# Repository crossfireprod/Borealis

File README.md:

Borealis
==================

WS2812/DMX Light Controller For the [ESPixelStick Firmware](https://github.com/forkineye/ESPixelStick) by Shelby Merrick (forkineye).  Hardware supports both DMX (RS-485) and Pixel (WS2811/WS2812) output modes.

**Key Features**
* The [NodeMCU](https://en.wikipedia.org/wiki/NodeMCU) DEVKIT 1.0 was chosen due to pricepoint, availability, form factor, and onboard 3.3v power supply / USB interface (programmer).  
* Either a DC barrel jack or 5.08mm pluggable terminals may be used to supply power.  
* Output power and data is provided via 5.08mm pluggable terminal blocks.  
* PTC is used in lieu of a traditional fuse.  
* Drill hole in PCB allows for use of reverse firing activity LED, if desired.

Bill Of Materials
-------------------

A Bill Of Materials detailing the specific parts used in our most recent production run can be found on Octopart.  Pricing is more or less optimized around single unit quanties.

* [Pixel (WS2811/WS2812) Version](https://octopart.com/bom-tool/HFxE4Ql2)
* [DMX (RS-485) Version](https://octopart.com/bom-tool/G0dtO20q)

Note: If desired, boards can be populated for both DMX and Pixel use.  (Output mode defined by firmware configuration.)

Repository Contents
-------------------

* **/Hardware** - Eagle Schematic & PCB Layout
* **/Software** - [Platformio](http://platformio.org/) project containing [ESPixelStick Firmware](https://github.com/forkineye/ESPixelStick).
* **/Images** - Images of the schematic / PCB design, as well as a fully assembled unit.

License
-------------------

All contents of this repository are released under [Creative Commons Share-alike 4.0](http://creativecommons.org/licenses/by-sa/4.0/).

Design By: Greg Pohodich & [*ZachCross.com*](https://ZachCross.com)

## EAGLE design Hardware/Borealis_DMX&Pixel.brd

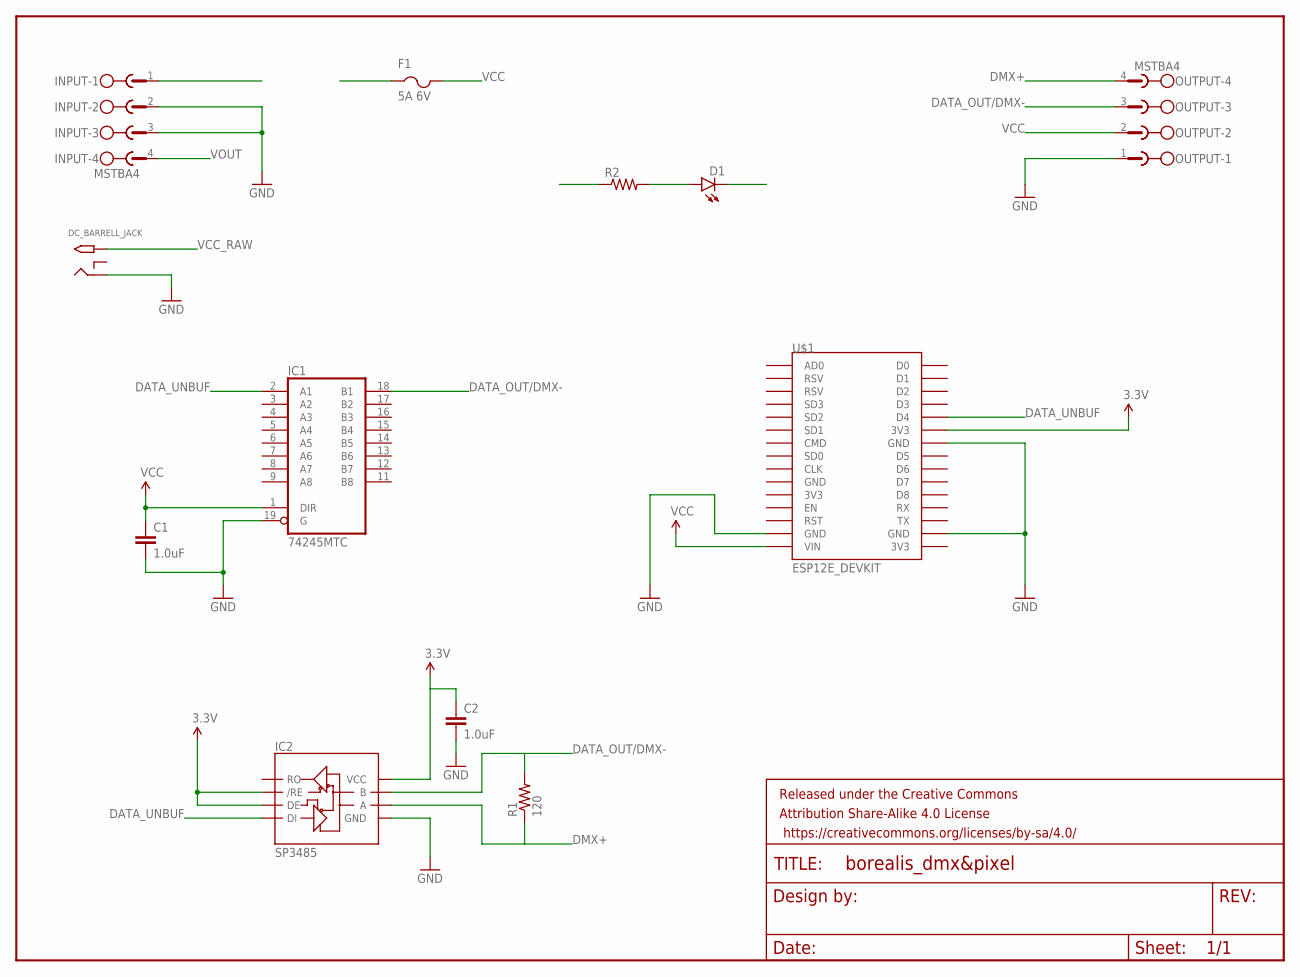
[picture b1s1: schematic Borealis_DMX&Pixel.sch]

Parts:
C1, C2: 1.0uF; 0603-CAP
D1: LED1206-BOTTOM; LED-1206-BOTTOM
DC_BARRELL_JACK: 2.1MMJACKTHM; PJ-102A
F1: 5A 6V; R1206
FRAME1: FRAME-LETTERNO_PACKAGE; DUMMY
IC1: 74245MTC; SSOP20
IC2: SP3485; SO08
INPUT: MSTBA4
OUTPUT: MSTBA4
R1: 120; 0603-RES
R2: RESISTOR0603-RES; 0603-RES
U$1: ESP12E_DEVKIT; DEV_LAYOUT

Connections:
3.3V: C2.1, IC2.2 (/RE), IC2.3 (DE), IC2.8 (VCC), U$1.3V3@1 (3V3)
DATA_OUT/DMX-: IC1.18 (B1), IC2.7 (B), OUTPUT.3, R1.2
DATA_UNBUF: IC1.2 (A1), IC2.4 (DI), U$1.D4
DMX+: IC2.6 (A), OUTPUT.4, R1.1
GND: C1.2, C2.2, D1.C, DC_BARRELL_JACK.RING, IC1.10 (GND), IC1.19 (G), IC2.5 (GND), INPUT.2, INPUT.3, OUTPUT.1, U$1.GND@1 (GND), U$1.GND@2 (GND), U$1.GND@3 (GND)
LED_PWR: D1.A, R2.2
VCC: C1.1, F1.2, IC1.1 (DIR), IC1.20 (VCC), OUTPUT.2, R2.1, U$1.VIN
VCC_RAW: DC_BARRELL_JACK.TIP, F1.1, INPUT.1
VOUT: INPUT.4

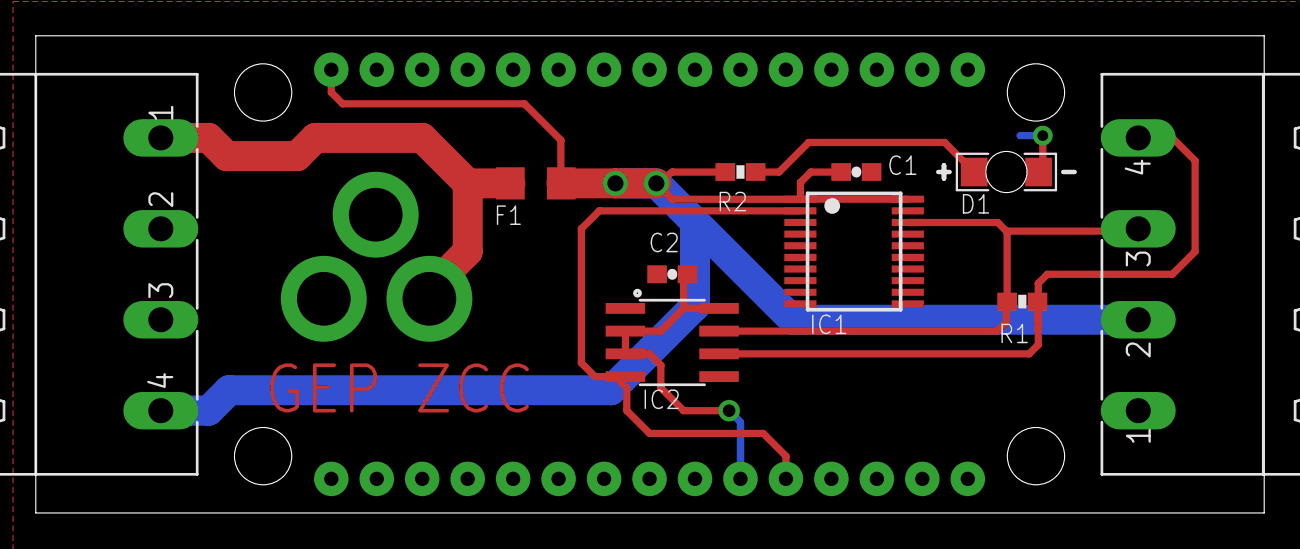
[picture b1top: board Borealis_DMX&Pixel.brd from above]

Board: 2 copper layers, 68.6 x 26.7 mm, 13 parts (1 on the bottom side), 8 nets.

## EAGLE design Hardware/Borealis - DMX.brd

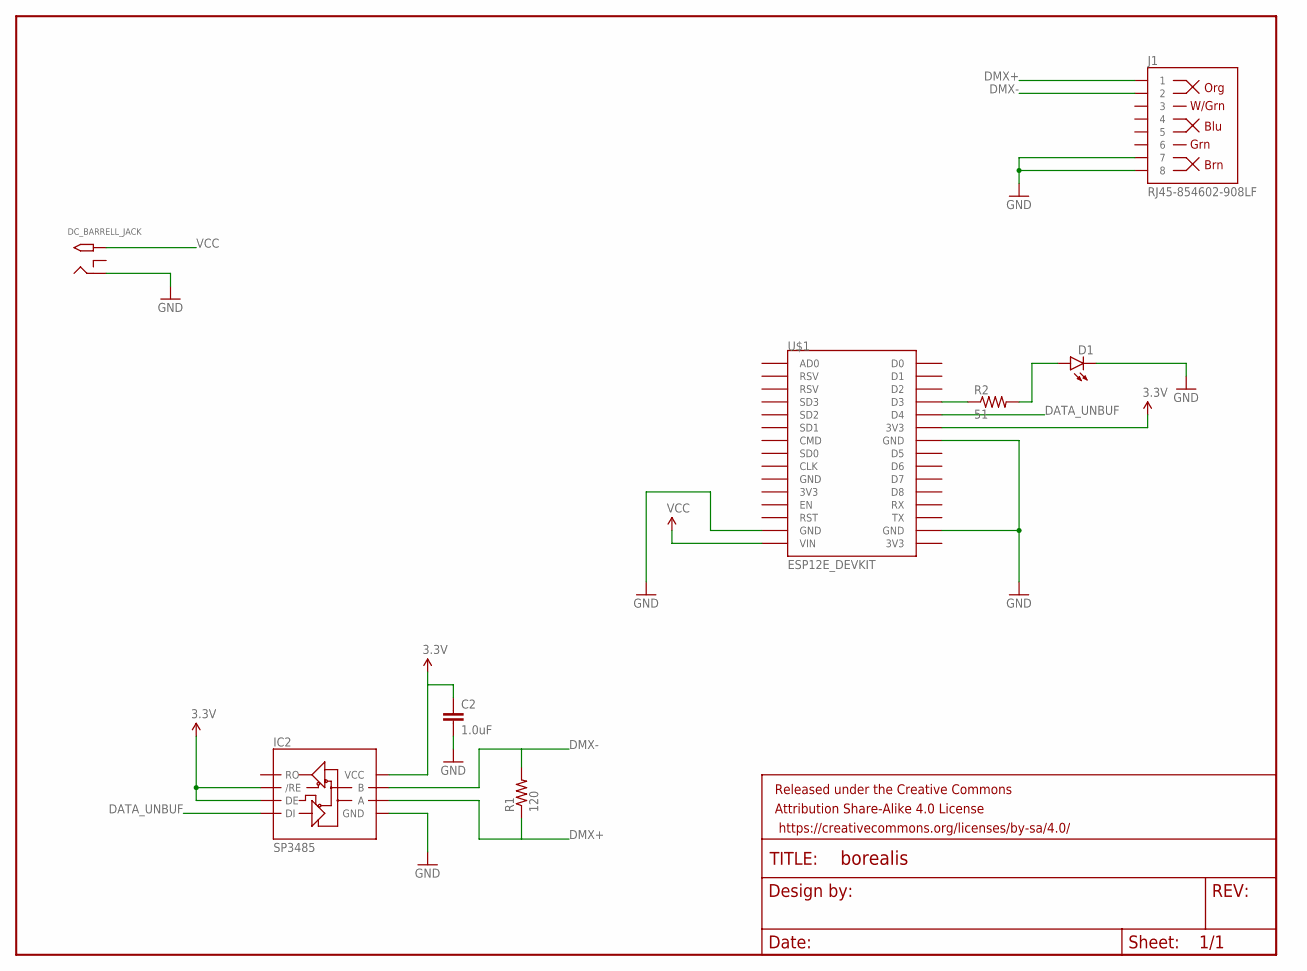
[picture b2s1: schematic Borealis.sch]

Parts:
C2: 1.0uF; 0603-CAP
D1: LED1206-BOTTOM; LED-1206-BOTTOM
DC_BARRELL_JACK: 2.1MMJACKTHM; PJ-102A
FRAME1: FRAME-LETTERNO_PACKAGE; DUMMY
IC2: SP3485; SO08
J1: RJ45-854602-908LF; RJ45-GREG
R1: 120; 0603-RES
R2: 51; 0603-RES
U$1: ESP12E_DEVKIT; DEV_LAYOUT

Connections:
3.3V: C2.1, IC2.2 (/RE), IC2.3 (DE), IC2.8 (VCC), U$1.3V3@1 (3V3)
DATA_UNBUF: IC2.4 (DI), U$1.D4
DMX+: IC2.6 (A), J1.1, R1.1
DMX-: IC2.7 (B), J1.2, R1.2
GND: C2.2, D1.C, DC_BARRELL_JACK.RING, IC2.5 (GND), J1.7, J1.8, U$1.GND@1 (GND), U$1.GND@2 (GND), U$1.GND@3 (GND)
LED_PWR: D1.A, R2.2
unnamed: R2.1, U$1.D3
VCC: DC_BARRELL_JACK.TIP, U$1.VIN

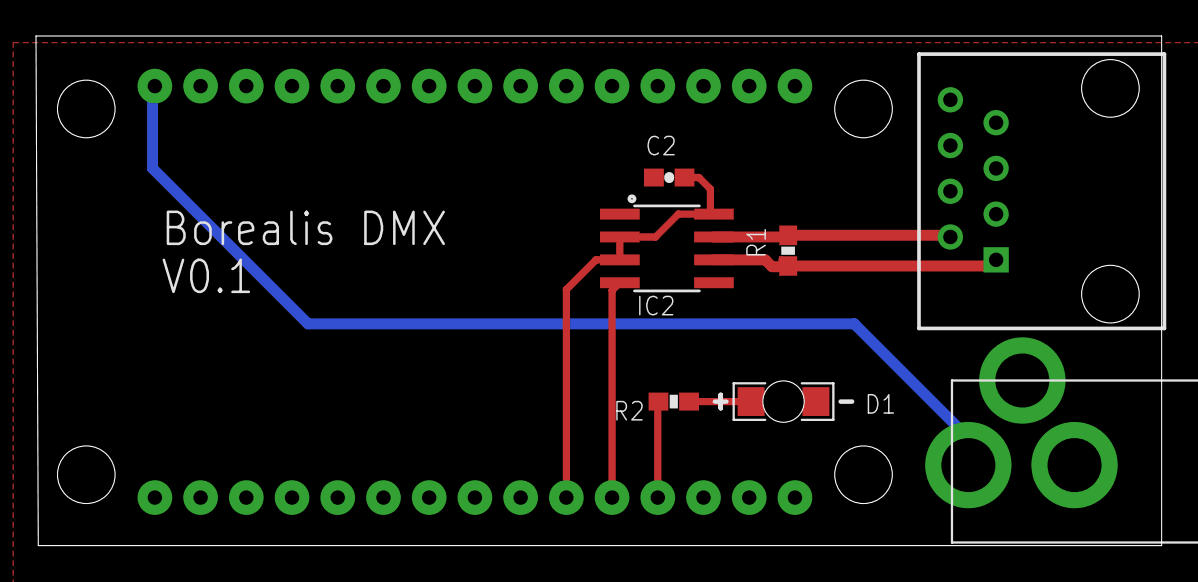
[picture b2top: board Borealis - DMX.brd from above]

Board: 2 copper layers, 62.5 x 28.3 mm, 9 parts (0 on the bottom side), 8 nets.

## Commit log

2017-08-03 Initial commit of design files, images, and README.
2017-08-03 Updated top profile image.
2017-08-03 README update
2017-08-03 Updating file names.
2017-08-03 Added Borealis Schematic
    Also sample images added
2017-08-03 Updated README to more clearly define output modes.
2017-10-29 Added ESPixelStick FW
2017-10-29 FW Dir Cleanup
2018-05-04 Replaced erroneously committed DMX only output design files with DMX & Pixel version refrenced in repo documentation.
2018-05-05 Resolved typo

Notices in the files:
parts and their libraries:
SparkFun-Capacitors: Licensing: Creative Commons ShareAlike 4.0 International - https://creativecommons.org/licenses/by-sa/4.0
SparkFun-Aesthetics: Released under the Creative Commons Attribution Share-Alike 4.0 License
SparkFun-Aesthetics: https://creativecommons.org/licenses/by-sa/4.0
